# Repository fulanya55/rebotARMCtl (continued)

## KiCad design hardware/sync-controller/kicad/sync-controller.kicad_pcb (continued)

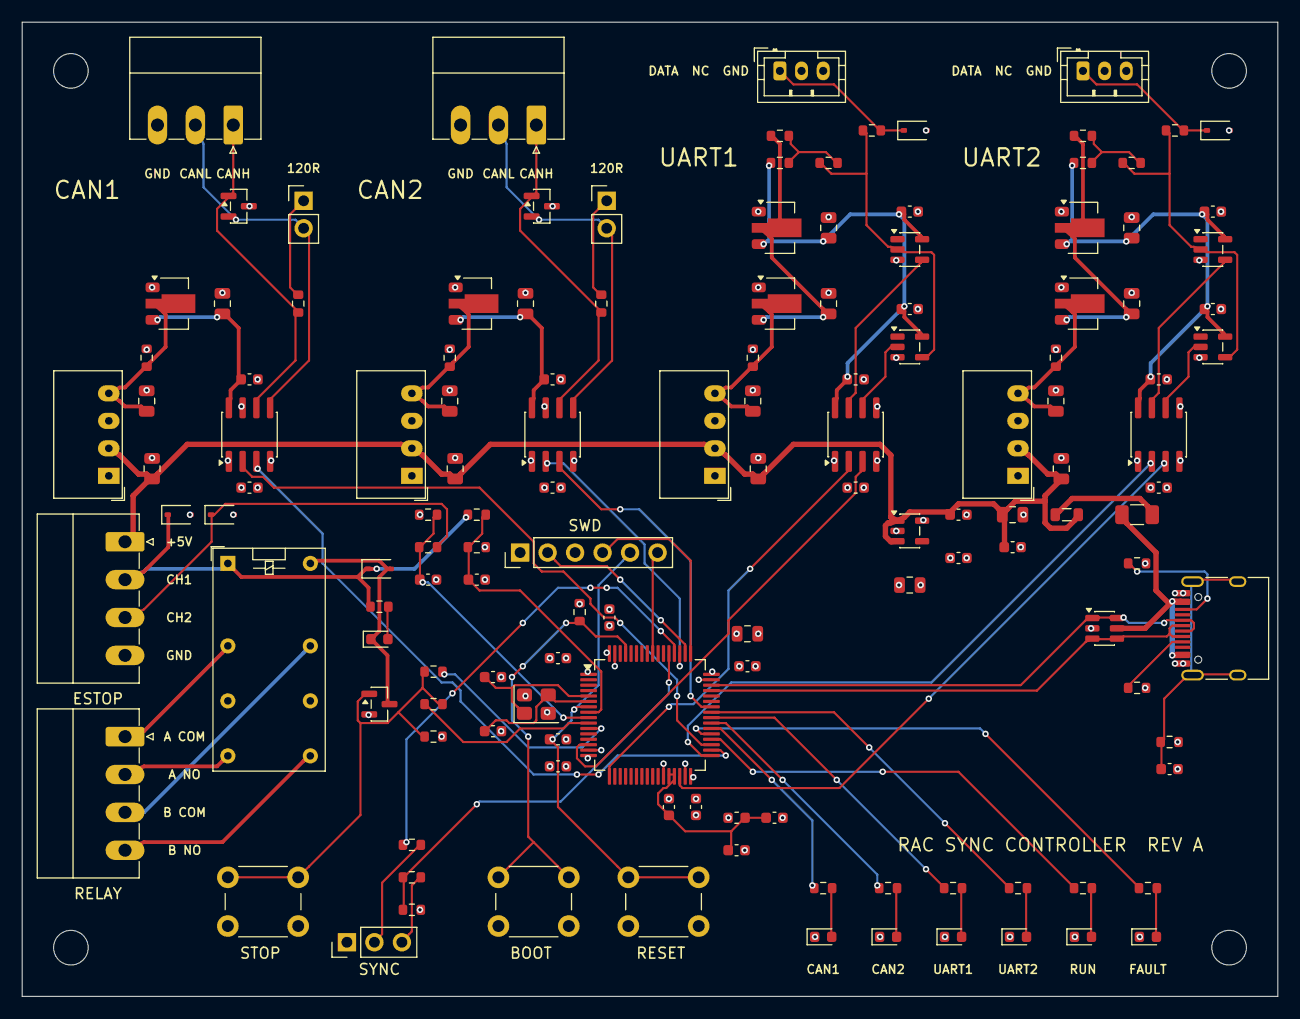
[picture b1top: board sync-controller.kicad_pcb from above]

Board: 4 copper layers, 116.0 x 90.0 mm, 140 parts (0 on the bottom side), 85 nets.

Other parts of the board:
H: MountingHole_3.2mm_M3
H#2, H#3, H#4: MountingHole_3.2mm_M3

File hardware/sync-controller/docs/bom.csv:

Qty,References,Value,Footprint,MPN,LCSC,Fit
1,C1,4.7nF,C_0603_1608Metric,,,yes
1,C2,10uF,C_0805_2012Metric,,,yes
24,C3 C6 C8 C9 C10 C11 C12 C14 C15 C18 C19 C20 C24 C25 C29 C30 C35 C36 C37 C38 C43 C44 C45 C46,100nF,C_0603_1608Metric,,,yes
2,C4 C7,1uF,C_0603_1608Metric,,,yes
12,C5 C13 C21 C23 C26 C28 C31 C33 C34 C39 C41 C42,4.7uF,C_0805_2012Metric,,,yes
2,C16 C17,18pF,C_0603_1608Metric,,,yes
4,C22 C27 C32 C40,10uF 25V,C_0805_2012Metric,,,yes
5,D1 D2 D3 D4 D10,green,LED_0603_1608Metric,,,yes
1,D5,blue,LED_0603_1608Metric,,,yes
1,D6,red,LED_0603_1608Metric,,,yes
4,D7 D8 D13 D14,PESD5V0,D_SOD-323,,,yes
1,D9,1N4148W,D_SOD-323,,,yes
2,D11 D12,NUP2105L,SOT-23,,,no
1,F1,750mA,Fuse_1206_3216Metric,SMD1206 750mA hold,,yes
1,FB1,600R@100MHz 1A,L_0805_2012Metric,,,yes
1,FB2,600R@100MHz,L_0603_1608Metric,,,yes
1,J1,USB-C,USB_C_Receptacle_HRO_TYPE-C-31-M-12,HRO TYPE-C-31-M-12,C165948,yes
1,J2,SWD,PinHeader_1x06_P2.54mm_Vertical,,,yes
1,J3,ESTOP,"PhoenixContact_MC_1,5_4-G-3.5_1x04_P3.50mm_Horizontal",,,yes
1,J4,RELAY,"PhoenixContact_MC_1,5_4-G-3.5_1x04_P3.50mm_Horizontal",,,yes
1,J5,SYNC,PinHeader_1x03_P2.54mm_Vertical,,,yes
2,J6 J8,TERM,PinHeader_1x02_P2.54mm_Vertical,,,yes
1,J7,CAN1,"PhoenixContact_MC_1,5_3-G-3.5_1x03_P3.50mm_Horizontal",,,yes
1,J9,CAN2,"PhoenixContact_MC_1,5_3-G-3.5_1x03_P3.50mm_Horizontal",,,yes
1,J10,UART1,JST_PH_B3B-PH-K_1x03_P2.00mm_Vertical,,,yes
1,J11,UART2,JST_PH_B3B-PH-K_1x03_P2.00mm_Vertical,,,yes
1,K1,G5V-2-DC5,Relay_DPDT_Omron_G5V-2,Omron G5V-2 DC5,,yes
1,Q1,2N7002,SOT-23,2N7002,,yes
2,R1 R2,5.1k,R_0603_1608Metric,,,yes
1,R3,1M,R_0603_1608Metric,,,yes
4,R4 R14 R15 R17,10k,R_0603_1608Metric,,,yes
10,R5 R6 R7 R8 R9 R10 R11 R12 R18 R20,1k,R_0603_1608Metric,,,yes
2,R13 R21,100k,R_0603_1608Metric,,,yes
1,R16,20k,R_0603_1608Metric,,,yes
3,R19 R30 R35,100,R_0603_1608Metric,,,yes
4,R22 R24 R26 R31,2.2k,R_0603_1608Metric,,,yes
2,R23 R25,120,R_0603_1608Metric,,,yes
2,R27 R32,680,R_0603_1608Metric,,,yes
2,R28 R33,0,R_0603_1608Metric,,,yes
2,R29 R34,0,R_0603_1608Metric,,,no
1,SW1,BOOT,SW_PUSH_6mm,,,yes
1,SW2,RESET,SW_PUSH_6mm,,,yes
1,SW3,STOP,SW_PUSH_6mm,,,yes
1,U1,USBLC6-2SC6,SOT-23-6,USBLC6-2SC6,,yes
1,U2,AP2112K-3.3,SOT-23-5,AP2112K-3.3TRG1,,yes
1,U3,STM32G474RET6,LQFP-64_10x10mm_P0.5mm,STM32G474RET6,,yes
4,U4 U7 U10 U16,B0509S-1WR3,Converter_DCDC_Murata_CRE1xxxxxxSC_THT,Mornsun B0509S-1WR3,,yes
4,U5 U8 U11 U17,HT7550-1,SOT-89-3,HT7550-1,,yes
2,U6 U9,ISO1044BD,SOIC-8_3.9x4.9mm_P1.27mm,ISO1044BD,C2878198,yes
2,U12 U18,HT7533-1,SOT-89-3,HT7533-1,,yes
2,U13 U19,ADuM1201BRZ,SOIC-8_3.9x4.9mm_P1.27mm,ADuM1201BRZ,,yes
2,U14 U20,74LVC1G07,SOT-23-5,SN74LVC1G07DBVR,,yes
2,U15 U21,74LVC1G17,SOT-23-5,SN74LVC1G17DBVR,,yes
1,Y1,8MHz CL12pF,Crystal_SMD_3225-4Pin_3.2x2.5mm,8 MHz 3225 12 pF,,yes

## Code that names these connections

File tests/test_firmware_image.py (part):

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
    # LQFP-64 positions, from ST's STM32_open_pin_data.
    PIN_NUMBER = {
        "PA2": "14",
        "PA3": "17",
        "PB10": "30",
        "PB11": "33",
        "PB12": "34",
        "PB13": "35",
        "PA8": "42",
        "PA15": "51",
        "PA11": "45",
        "PA12": "46",
        "PC0": "8",
        "PC1": "9",
        "PC2": "10",
        "PC3": "11",
        "PC6": "38",
        "PC7": "39",
        "PC8": "40",
        "PC9": "41",
        "PB14": "36",
        "PB15": "37",
        "PC10": "52",
        "PC11": "53",
    }

    EXPECTED = {
        "PA2": "UART1_TX",
        "PA3": "UART1_RX",
        "PB10": "UART2_TX",
        "PB11": "UART2_RX",
        "PB12": "CAN1_RX",
        "PB13": "CAN1_TX",
        "PA8": "CAN2_RX",
        "PA15": "CAN2_TX",
        "PA11": "USB_DM",
        "PA12": "USB_DP",
        "PC0": "ESTOP_SENSE1",
        "PC1": "ESTOP_SENSE2",
        "PC2": "SAFETY_EN",
        "PC3": "STOP_SENSE",
        "PC6": "LED_CAN1",
        "PC7": "LED_CAN2",
        "PC8": "LED_UART1",
        "PC9": "LED_UART2",
        "PB14": "LED_RUN",
        "PB15": "LED_FAULT",
        "PC10": "SYNC_OUT",
        "PC11": "SYNC_IN",
    }

    def test_schematic_nets_match_the_pin_map(self):
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        for define, port, pin in (
            ("ESTOP_CH1", "GPIOC", 0),
            ("ESTOP_CH2", "GPIOC", 1),
            ("SAFETY_EN", "GPIOC", 2),
            ("STOP_SENSE", "GPIOC", 3),
            ("SYNC_OUT", "GPIOC", 10),
            ("SYNC_IN", "GPIOC", 11),
        ):
            assert re.search(rf"{define}_PORT {port}\b", board), define
            assert re.search(rf"{define}_PIN {pin}u", board), define
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
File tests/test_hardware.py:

"""The committed board against its checks. Skipped on machines without KiCad."""

from __future__ import annotations

import os
import shutil
import subprocess
import sys
from pathlib import Path

import pytest

ROOT = Path(__file__).resolve().parents[1]
HW = ROOT / "hardware" / "sync-controller"
GEN = HW / "gen"
CLI = os.environ.get("KICAD_CLI", "D:/KiCad/bin/kicad-cli.exe")
KICAD_PY = os.environ.get("KICAD_PYTHON", "D:/KiCad/bin/python.exe")

sys.path.insert(0, str(GEN))

needs_kicad = pytest.mark.skipif(not (Path(CLI).exists() or shutil.which(CLI)), reason="KiCad is not installed")


def run(script: str, python: str = sys.executable) -> str:
    env = {**os.environ, "PYTHONUTF8": "1"}
    result = subprocess.run([python, script], cwd=GEN, capture_output=True, text=True, encoding="utf-8", errors="replace", env=env)
    assert result.returncode == 0, result.stdout[-2000:] + result.stderr[-1000:]
    return result.stdout


@needs_kicad
def test_erc_is_clean():
    assert "unexplained: 0" in run("check_erc.py")


@needs_kicad
def test_schematic_matches_the_design_data():
    assert ", 0 mismatches" in run("check_netlist.py")


@needs_kicad
def test_drc_is_clean_and_matches_the_schematic():
    assert "unexplained: 0" in run("check_drc.py")


@needs_kicad
def test_isolation_gaps_meet_the_target():
    run("check_isolation.py", KICAD_PY)


class TestDesignRules:
    """Circuit properties the safety and isolation arguments depend on."""

    @pytest.fixture(scope="class")
    def sheets(self):
        from design import build

        return {s.name: s for s in build()}

    def _part(self, sheet, value):
        return next(p for p in sheet.parts if p.value == value)

    def test_every_port_has_its_own_ground(self, sheets):
        for name in ("port_can1", "port_can2", "port_uart1", "port_uart2"):
            sheet = sheets[name]
            converter = self._part(sheet, "B0509S-1WR3")
            assert converter.pins["1"] == "GND" and converter.pins["2"] == "+5V"
            assert converter.pins["3"] == "ISO_GND" and converter.pins["4"] == "ISO_9V"

    def test_can_transceiver_pins_follow_the_datasheet(self, sheets):
        """TI SLLSFB0A: 5 CANL, 6 CANH, 7 GND2, 8 VCC2. Easy to misremember."""
        iso = self._part(sheets["port_can1"], "ISO1044BD")
        assert iso.pins["5"] == "CANL"
        assert iso.pins["6"] == "CANH"
        assert iso.pins["7"] == "ISO_GND"
        assert iso.pins["8"] == "ISO_5V", "VCC2 must be the regulated rail: its limit is 5.5 V"

    def test_servo_connector_leaves_the_arms_supply_unconnected(self, sheets):
        connector = next(p for p in sheets["port_uart1"].parts if p.footprint.endswith("PH_B3B-PH-K_1x03_P2.00mm_Vertical"))
        assert "2" not in connector.pins
        assert "2" in connector.no_connect

    def test_the_estop_contact_is_in_series_with_the_relay_coil(self, sheets):
        safety = sheets["safety"]
        terminal = next(p for p in safety.parts if p.value == "ESTOP")
        relay = next(p for p in safety.parts if p.lib == "Relay:G5V-2")
        mosfet = next(p for p in safety.parts if p.value == "2N7002")
        assert terminal.pins["1"] == "+5V"
        assert relay.pins["1"] == terminal.pins["2"], "coil is fed through the contact"
        assert relay.pins["16"] == mosfet.pins["3"]

    def test_the_relay_gate_is_pulled_down(self, sheets):
        """A reset MCU leaves its pin floating: this is what then drops the relay."""
        safety = sheets["safety"]
        pulldowns = [p for p in safety.parts if p.value == "100k" and set(p.pins.values()) == {"SAFETY_GATE", "GND"}]
        assert len(pulldowns) == 1

    def test_relay_outputs_are_normally_open(self, sheets):
        terminal = next(p for p in sheets["safety"].parts if p.value == "RELAY")
        assert set(terminal.pins.values()) == {"K_A_COM", "K_A_NO", "K_B_COM", "K_B_NO"}

    def test_no_port_signal_bypasses_an_isolator(self, sheets):
        """On a port sheet only the isolator and converter may touch both domains."""
        from design import GLOBALS, POWER_NETS

        for name in ("port_can1", "port_can2", "port_uart1", "port_uart2"):
            for part in sheets[name].parts:
                nets = set(part.pins.values())
                logic = nets & (GLOBALS | POWER_NETS)
                isolated = nets - logic
                if logic and isolated:
                    assert part.value in ("B0509S-1WR3", "ISO1044BD", "ADuM1201BRZ"), f"{part.ref} {part.value} joins {nets}"

    def test_bom_lists_every_part(self):
        import csv

        from design import all_parts

        with (HW / "docs" / "bom.csv").open(encoding="utf-8") as handle:
            rows = list(csv.DictReader(handle))
        assert sum(int(r["Qty"]) for r in rows) == len(all_parts())


def test_manufacturing_files_exist():
    fab = HW / "fab"
    if not fab.exists():
        pytest.skip("run make_all.py first")
    names = {p.name for p in (fab / "gerber").iterdir()}
    for layer in ("F_Cu", "In1_Cu", "In2_Cu", "B_Cu", "Edge_Cuts"):
        assert any(layer in n for n in names), layer
    assert any(n.endswith(".drl") for n in names)
    assert (fab / "positions.csv").exists()
    assert (fab / "sync-controller-gerbers.zip").exists()
